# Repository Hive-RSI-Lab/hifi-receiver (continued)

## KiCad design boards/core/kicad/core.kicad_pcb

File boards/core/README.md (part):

# core: the Plus/Ultra main board

The main board of hifi-receiver-2's **Plus** and **Ultra** tiers
([docs/product.md](../../docs/product.md)). It is a USB-C-powered
streaming amplifier on one 4-layer board, 154.4 x 113 mm (120 x 100 until the
banana sockets; see below):

- **Input:** 28 V USB PD EPR at up to 140 W.
- **Streaming:** ESP32 with Wi-Fi, Bluetooth and Ethernet.
- **Mains DAC:** Sabre ES9018K2M.
- **Subwoofers:** a separate sub DAC for two sub outputs.
- **Line in:** RCA, with a zero-latency "DJ direct" path.
- **Amp:** two TPA3220 class-D amps (the pad-down TPA3221): 2 x 77 W into 4 ohm peak, no heatsink. Plus plays L on zone A and R on zone B; Ultra drives two pairs.
- **Ultra population options:** a second amp (zone B), an optical input
  and the FFC to the `ultra-front` display board.

It was designed with the hive-hwde module (KiCad 10, JLCPCB) on 2026-10-28,
from schematic through routed layout to a JLC fab package. **Nothing has
been ordered. Ordering is the person's.**

## Status (2026-10-29)

All hwde gates pass on the routed board after the first-spin review ECO, with hive-hwde at c23e27e:

| Gate | Result |
|---|---|
| `erc` | 0 errors, 0 warnings |
| `place` | pass |
| `drc_routed` | 0 errors, 0 warnings, parity clean |
| `verify` | pass, 1 waiver (`reports/verify-waivers.json`: the ESP32 module's 3V3 decoupling loop) |
| `dfm` | pass on the exported Gerbers |

The fab package is in `fab/`:

- **Gerbers:** `core_gerbers.zip`.
- **Plus build:** `BOM.csv` (88 lines, every one with an LCSC number), `CPL.csv` (298 placed parts, 14 of them on the bottom: see `fab/ORDERING.md`), `BOM-full.csv` and `prebuy.csv`, which lists the Extended parts.
- **Ultra build:** `fab/ultra/` holds `BOM.csv` and `CPL.csv` (302 placed parts) for the same Gerbers.

Board facts:

- **Size:** 4 layers, 154.4 x 113 mm overall, 1.6 mm. The right-hand 34.4 mm
  is a wing along the rear only (y < 150 in KiCad); the front right stays
  notched so the ESP32's antenna is still at the board edge.
- **Stackup:** 4 layers, 1.6 mm, 1 oz outer and 1 oz inner. JLC04161H-1080B
  comes only with 0.5 oz inner, so leave Specify Stackup at no requirement
  on the quote page: JLC then builds a 0.203 mm 7628 prepreg and a 1.03 mm
  core, and a named 1 oz layup adds $51.20. No net here is impedance
  controlled. Order it with
  epoxy filled and capped vias (`fab/ORDERING.md`), and inner copper 1 oz, not JLC's 0.5 oz default: the In2 VBUS/PVDD planes carry
  the full 5 A on their own (`power_trunk.py`).
- **Vias:** 0.7/0.3 mm, plus a few 0.45/0.2 mm GND taps.
- **Mounting:** 4 x M3 plated holes.
- **Holes:** JLC's 0.5 mm hole-to-hole spacing is held everywhere.

hwde's own estimate for 10 boards with assembly is $278, $27.84 each. That
excludes the parts, and it is a lower bound: the PCB line has the
oversize-area bug that hive-hwde issue #12 fixes. JLC's cart is the real quote.

## What's on it

The full block list, the ESP32 GPIO map, the I/O expander map, the FFC
pinout and the power tree are in
[architecture/blocks.md](architecture/blocks.md). In short:

| Block | Parts |
|---|---|
| Power in | GCT USB4085-GF-A through-hole USB-C (48 V/5 A, 240 W), CH224Q PD sink (asks for 28 V; ESP32 can read it or change it over I2C), SMBJ30A TVS, 10 mΩ shunt + INA186 current sense |
| PVDD switch | AO4485 P-FET, on only when firmware sets PVDD_EN **and** the CH224Q's PG says the contract is good; ~60 ms soft start (0.47 A, 9.8 W peak); gross-overvoltage cut-off |
| Rails | SY8303 VBUS to 5.1 V; SY8089 5 V to 3.3 V; LP5907 3.3 V analog; ferrite-fed +5VA and +3V3E |
| Processor | ESP32-WROVER-E-N8R8; CH340B USB-serial on the same USB-C (auto-reset, flashing from a laptop) |
| Ethernet | LAN8720A + HR911105A magjack, gated 50 MHz RMII clock |
| Mains DAC | ES9018K2M at 49.152 MHz MCLK, OPA1678 differential-to-single-ended stage |
| Sub DAC | PCM5102A to a stacked dual RCA (SUB1, SUB2) |
| Line in | stacked dual RCA, ES7243E ADC, TS5A23157 DAC/DJ-direct selector |
| Self-measurement | zone A's A_SPK_L+/R+ through 150k/10k, 470 pF, 1 uF onto a 1.65 V bias; TS5A23157 U20 picks RCA input (default) or the taps for the ADC; select from expander P17 through Q7 |
| Zone A amp | TPA3220 (24 dB, AD mode, 600 kHz; pad down, 15 vias into the GND planes), 10 µH / 10 A filters, 4 board-mounted 4 mm banana sockets |
| Zone B amp [Ultra] | the same, synchronised to zone A as a peripheral |
| Control | TCA9539 I/O expander (0x74, reset with the ESP32's EN); Plus front-edge knob, 2 buttons, IR receiver, status LED |
| Optical [Ultra] | PLR237 TOSLINK into the ES9018K2M's S/PDIF mux |
| Front board [Ultra] | 20-pin 0.5 mm FFC to `ultra-front` |

## Plus and Ultra from one board

| Parts | Plus | Ultra |
|---|---|---|
| zone B amp, its filters, bulk cap (U16, L5-L8, C3xx/R3xx) | fitted (plays R) | fitted |
| speaker sockets J20/J21 (zone A L), J26/J27 (zone B R) | fitted | fitted |
| speaker sockets J22/J23 (zone A R), J24/J25 (zone B L) | not fitted | fitted |
| TOSLINK U19, FB3, C126 | not fitted | fitted |
| FFC J3, R402/R403 | not fitted | fitted |
| knob SW1, buttons SW2/SW3, IR U18 (+R400/C400) | fitted | not fitted |

`fab/BOM.csv`/`CPL.csv` are the **Plus** build. `fab/ultra/BOM.csv` and
`CPL.csv` are the **Ultra** build of the same Gerbers.

## Banana sockets (2026-11-01, issues #117, #124)

The speaker outputs are eight 4 mm banana sockets in one row along the rear
edge, 11 mm apart. From the left in KiCad (from behind the box it reads
right to left): J20 A L+, J21 A L-, J22 A R+, J23 A R-, J24 B L+, J25 B L-,
J26 B R+, J27 B R-. Red is +. Plus plays L on zone A and R on zone B
(`HIFI_SPLIT`), so it fits J20/J21 and J26/J27; Ultra fits all eight.

A socket reaches 21.4 mm into the board and its nose stands 2.65 mm past the
edge, so the board grew. The rear edge moved 13 mm back, and a 34.4 mm wing
on the right took the RCA jacks J4/J5 and the TOSLINK U19. They moved with
D7/D8, FB3 and C126 and the copper between them as one block. The mounting
holes H1/H2 went to the new rear corners (H2 later moved south along the east edge to (185.45, 127.4), to make room for the jacks' side ears: `kicad/gen/rca_ear_eco.py`). How it was done, from
`boards/core`, KiCad's python as `python3.11`:

1. `kicad/gen/blocks_amp.py`: the sockets replace the terminals. Then
   `hwde lib_pull --lcsc C7437321 C7437322`, `build.py` (only amp_a/amp_b
   kept), `parts/*.json` by hand, and the netlist.
2. `python3.11 kicad/gen/banana_eco.py kicad/core.kicad_pcb`: rips the old
   terminal copper and the stitch vias under the row, and cuts the speaker
   pours back to y 130. It moves the rear block and the holes, and redraws
   the outline and the planes.
3. `hwde board_update --placements kicad/gen/banana_placements.json`.
4. `python3.11 kicad/gen/banana_route.py kicad/core.kicad_pcb`: one
   staircase pour per speaker net from its old pour to its socket's pin 2.
   L-/R+ run on F.Cu and L+/R- on B.Cu, four per layer, with no crossings
   and no vias. The pours are 2 mm wide (3.7 A rms). Where a later band
   crosses below a socket, its pin 1 joins pin 2 by a 1 mm In2 link (J23,
   J24, J25).
5. `python3.11 kicad/gen/banana_snub.py kicad/core.kicad_pcb`: zone A R- and
   zone B L+'s snubbers reached their net through the old terminal pin. Each
   gets a via and a B.Cu stub into its pour.
6. `miniroute.py` relays SUB1/SUB2_OUT, LIN_L/LIN_R and OPT_SPDIF to the
   moved block. Each line still goes into its ESD clamp (D7/D8) before the
   jack. Stale stubs are ripped with `rip_at.py`, and
   `kicad/gen/banana_silk.py` drops the sockets' silk, as on Lite.
   `kicad/gen/banana_45.py` puts the route ends back on the 45-degree grid
   (hwde check_route_style).

Folded in from review 5: R5-PA-1 (C4 220 nF/50 V C344195, C8 4.7 uF/25 V
C1779: Q1's soft start stays in its SOA), the EP paste windows off the vias
for U9/U10/U13 (`kicad/gen/ep_paste.py`, hwde check_ep_paste), and the
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
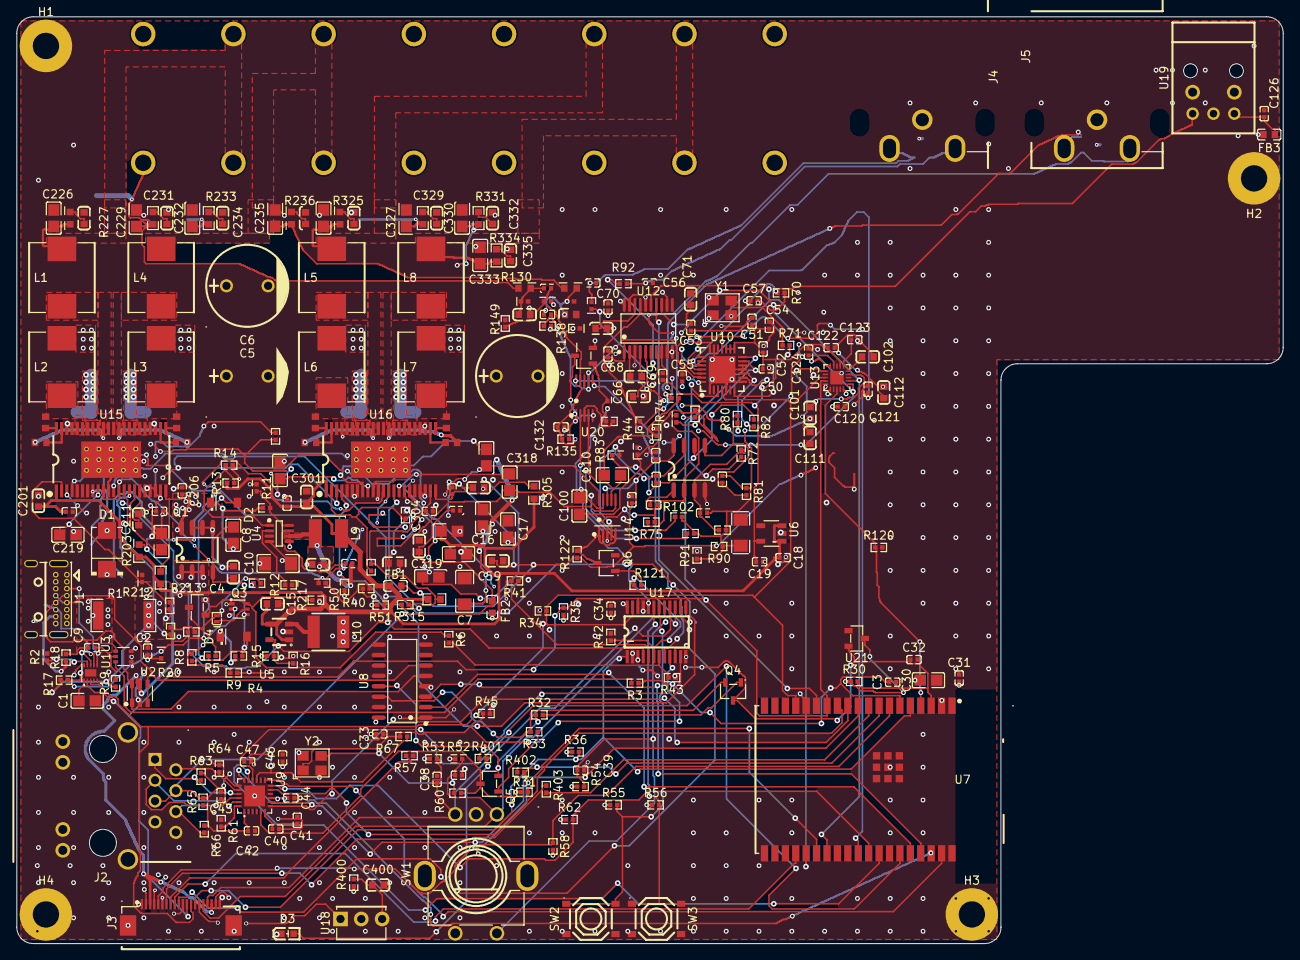
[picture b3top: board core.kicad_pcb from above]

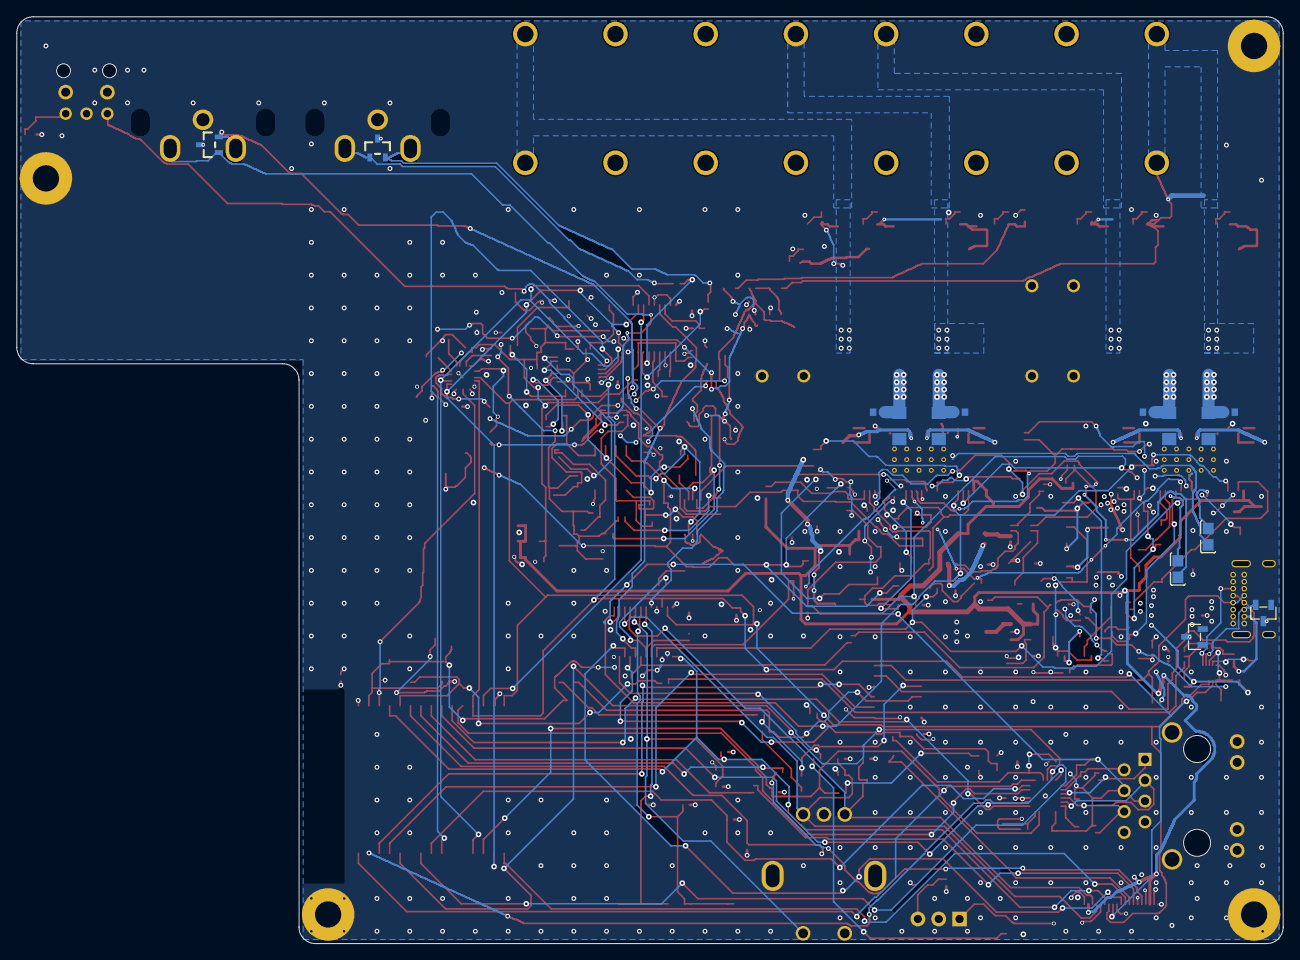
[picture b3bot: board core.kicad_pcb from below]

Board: 4 copper layers, 154.4 x 113.0 mm, 312 parts (14 on the bottom side), 190 nets.

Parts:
C1, C226, C229, C232, C235, C324, C327, C330, C333: 1uF; C0805
C2, C9, C31, C33, C34, C41, C42, C43, C44, C45, C46, C51, C53, C54, C55, C57, C58, C120, C121, C125, C126, C132, C202, C302: 100nF; C0402
C3, C12, C37, C38, C39: 10nF; C0402
C4: 220nF; C0603
C5, C6, C311: 470uF/50V; CAP-TH_BD10.0-P5.00-D1.0-FD
C7, C10: 10uF; C1206
C8, C100, C110: 4.7uF; C0805
C11, C208, C210, C308, C310: 100nF; C0603
C13, C14, C16, C17, C30: 22uF; C0805
C15, C21, C22, C59, C201, C301: 10uF; C0603
C18, C19, C32, C40, C47, C50, C52, C68, C69, C70, C122, C123, C124, C131, C137, C204, C206, C304, C306: 1uF; C0402
C56, C101, C102, C111, C112, C400: 4.7uF; C0603
C64: 100uF; C1206
C65, C66, C67: 2.2uF; C0603
C71, C72, C142, C143, C150, C151: 1nF; C0402
C130, C136: 470pF; C0603
C207, C209, C307, C309: 1uF; C1206
C211, C222, C223, C224, C225, C312, C320, C321, C322, C323: 33nF; C0603
C218, C219, C220, C221, C316, C317, C318, C319: 10uF; C0805
C228, C231, C234, C237, C326, C329, C332, C335: 470nF; C0603
D1: SMBJ30A; SMB_L4.6-W3.6-LS5.3-RD
D2: BZT52C33; SOD-123_L2.7-W1.6-LS3.7-RD
D3: KT-0603R; LED-SMD_L1.6-W0.8-R-RD
D4: BZT52C15; SOD-123_L2.7-W1.6-LS3.7-RD
D5: BAS16L; SOD-882_L1.0-W0.6-RD
D6, D9: NUP2105L; SOT-23-3_L2.9-W1.3-P1.90-LS2.4-BL-2
D7, D8: PESD5V0S2BT; SOT-23_L2.9-W1.3-P1.90-LS2.4-BR
FB1, FB2, FB3: 120R; L0603
H1, H2, H3, H4: MountingHole_3.2mm_M3_Pad
J1: USB4085-GF-A; USC-C-SMD_USB4085-GF-A
J2: HR911105A; RJ45-TH_HR911105A
J3: FFC 20P; FPC-SMD_20P-P0.50_XUNPU_FPC-05F-20PH20
J4: SUB OUT; CONN-TH_XDJK-0271-1650
J5: LINE IN; CONN-TH_XDJK-0271-1650
J20, J22, J24, J26: 24.243 red; CONN-TH_24.243.1_RED
J21, J23, J25, J27: 24.243 black; CONN-TH_24.243.2
L1, L2, L3, L4, L5, L6, L7, L8: 10uH; IND-SMD_L8.5-W8.0_PCC-M0854M
L9: 4.7uH; IND-SMD_L4.0-W4.0
L10: 2.2uH; IND-SMD_L4.0-W4.0_LQH44PN2R2MP0L
Q1: AO4485; SOIC-8_L5.0-W4.0-P1.27-LS6.0-BL
Q2: 2N7002; SOT-23-3_L2.9-W1.3-P1.90-LS2.4-BR
Q3: MMDT3904; SOT-363_L2.0-W1.3-P0.65-LS2.1-TL
Q4, Q5, Q6, Q7: S8050; SOT-23-3_L3.0-W1.7-P0.95-LS2.9-BR
R1: 10m; R2512
R2: 210k; R0402
R3, R6: 1k; R0402
R4, R5: 470k; R0402
R7, R10, R11, R12, R15, R40, R41, R42, R43, R44, R102, R112, R120, R132, R134, R138, R149, R150, R213, R214, R215, R404: 100k; R0402
R8, R9, R20, R30, R31, R32, R33, R36, R50, R51, R52, R53, R54, R55, R56, R57, R58, R67, R70, R121, R122, R131, R135, R137: 10k; R0402
R13: 15k; R0402
R14, R72, R74, R80, R82: 2k; R0402
R16: 22k; R0402
R17, R18, R19: 10R; R0402
R34, R35, R45: 2.2k; R0402
R60, R71, R402, R403: 33R; R0402
R61: 12k; R0402
R62: 1.5k; R0402
R63, R64, R65, R66: 49.9R; R0402
R73, R75, R81, R83: 1.3k; R0402
R90, R91, R92, R93, R401: 470R; R0402
R100, R101, R110, R111: 4.7k; R0402
R130, R136: 150k; R0603
R133, R216, R217, R314: 47k; R0402
R203, R205, R227, R230, R233, R236, R303, R305, R325, R328, R331, R334: 4.7R; R0603
R212: 20k; R0402
R313: 75k; R0402
R315: 0R; R0402
R400: 100R; R0402
SW1: EC11; SW-TH_EC11E1820402
SW2: BTN1; SW-SMD_4P-L5.1-W5.1-P3.70-LS6.5-TL_H1.5
SW3: BTN2; SW-SMD_4P-L5.1-W5.1-P3.70-LS6.5-TL_H1.5
U1: CH224Q; DFN-10_L2.0-W2.0-P0.40-BL-EP
U2: USBLC6-2SC6; SOT-23-6_L2.9-W1.6-P0.95-LS2.8-BL
U3: INA186A1; SC-70-6_L2.2-W1.3-P0.65-LS2.1-BR
U4: SY8303AIC; TSOT-23-8_L2.9-W1.6-P0.65-LS2.8-BR
U5: SY8089A1AAC; TSOT-23-5_L2.9-W1.6-P0.95-LS2.8-BR
U6: LP5907-3.3; SOT-23-5_L3.0-W1.7-P0.95-LS2.8-BR
U7: ESP32-WROVER-E-N8R8; WIFI-SMD_ESP32-WROVER-IE8MB
U8: CH340B; SOP-16_L10.0-W3.9-P1.27-LS6.0-BL
U9: LAN8720A; QFN-24_L4.0-W4.0-P0.50-BL-EP2.6
U10: ES9018K2M; QFN-28_L5.0-W5.0-P0.50-BL-EP3.3
U11: OPA1678; SOIC-8_L5.0-W4.0-P1.27-LS6.0-BL
U12: PCM5102A; TSSOP-20_L6.5-W4.4-P0.65-LS6.4-BL
U13: ES7243E; QFN-20_L3.0-W3.0-P0.40-BL-EP1.7
U14, U20: TS5A23157; MSOP-10_L3.0-W3.0-P0.50-LS5.0-BL
U15, U16: TPA3220; HTSSOP-44-1EP_L14.0-W6.1-P0.64-LS8.1-EP7.3x4.43
U17: TCA9539; TSSOP-24_L7.8-W4.4-P0.65-LS6.4-BL
U18: IRM-3638T; OPTO-TH_IRM-3638T
U19: PLR237/T8BK; OPTO-TH_PLR237-T10BK
U21: TLV803S; SOT-23-3_L2.9-W1.3-P1.90-LS2.4-BR
Y1: 49.152MHz; OSC-SMD_4P-L3.2-W2.5-BL
Y2: 50MHz; OSC-SMD_4P-L3.2-W2.5-BL

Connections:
+3V3: C2.1, C16.1, C17.1, C30.1, C31.1, C33.1, C34.1, C44.1, C46.1, C55.1, C57.1, C70.1, C120.1, C121.1, FB2.1, FB3.1, J3.2, J3.19, L10.2, R15.1, R20.1, R30.1, R31.1, R34.1, R35.1, R36.1, R50.1, R51.1, R52.1, R53.1, R54.1, R55.1, R56.1, R58.1, R62.1, R132.2, R138.2, R400.1, U3.3, U7.2, U8.4, U8.16, U9.9, U10.18, U12.20, U13.1, U13.5, U17.24, U21.3, Y1.1, Y1.4, Y2.4
+3V3A: C19.1, C50.1, C51.1, C52.1, C53.1, C54.1, C68.1, C69.1, C122.1, U6.5, U10.15, U10.16, U10.17, U12.1, U12.8, U13.12
+3V3E: C22.1, C42.1, C43.1, C45.1, FB2.2, J2.4, J2.5, R63.2, R64.2, R65.2, R66.2, U9.1, U9.19
+5V: C13.1, C14.1, C15.1, C18.1, C201.1, C202.1, C301.1, C302.1, FB1.1, J3.3, J3.18, L9.2, R13.1, R203.1, R205.1, R303.1, R305.1, U2.5, U5.1, U5.4, U6.1, U6.3, U15.1, U16.1
+5VA: C21.1, C58.1, C59.1, C125.1, C132.1, FB1.2, R90.1, R122.1, R135.1, U11.8, U14.8, U20.8
/AMP_A_RST: R40.1, U15.10, U17.4
/AMP_B_RST: R41.1, U16.10, U17.5
/AMP_FAULT: R50.2, U15.4, U16.4, U17.13
/AMP_IN_L: C218.1, C316.1, U14.10
/AMP_IN_R: C220.1, C318.1, U14.6
/AMP_OSCM: R216.1, U15.12, U16.12
/AMP_OSCP: R217.1, U15.13, U16.13
/AMP_OTW: R51.2, U15.3, U16.3, U17.14
/A_SPK_L+: C229.1, J20.1, J20.2, L2.2, R130.1, R230.1
/A_SPK_R+: C235.1, J22.1, J22.2, L4.2, R136.1, R236.1
/BTN_1: R55.2, SW2.1, SW2.2, U17.18
/BTN_2: R56.2, SW3.1, SW3.2, U17.19
/DAC_EN: R44.1, U10.28, U12.17, U17.8
/DJ_DIRECT: R42.1, R121.1, U17.6
/ENC_A: C37.1, J3.16, R52.2, SW1.A, U17.15
/ENC_B: C38.1, J3.17, R53.2, SW1.B, U17.16
/ENC_SW: C39.1, R54.2, SW1.D, U17.17
/ETH_CLK: Q5.3, R31.2, R60.2, U7.25, U9.5
/EXP_INT: J3.14, R36.2, U7.5, U17.1
/I2C_SCL: J3.12, R35.2, U1.2, U7.13, U10.3, U13.19, U17.22
/I2C_SDA: J3.13, R34.2, U1.3, U7.16, U10.4, U13.18, U17.23
/I2S_BCK: U7.24, U10.27, U12.13, U13.6
/I2S_DIN: R120.1, U7.4, U13.3
/I2S_DOUT_MAIN: U7.29, U10.25
/I2S_DOUT_SUB: U7.14, U12.14
/I2S_LRCK: U7.26, U10.26, U12.15, U13.7
/IR_IN: J3.15, R58.2, U7.7, U18.1
/ISENSE: C3.1, R3.2, U7.6
/LCD_BL: J3.10, U17.10
/LCD_CS: J3.8, R57.1
/LCD_DC: J3.9, U7.23
/LCD_MOSI: R403.1, U7.9
/LCD_SCLK: R402.1, U7.8
/LED_STATUS: R401.1, U17.11
/MAIN_L: C143.2, R75.2, U11.1, U14.2
/MAIN_R: C151.2, R83.2, U11.7, U14.4
/MDC: U7.37, U9.13
/MDIO: R62.2, U7.30, U9.12
/OPT_SPDIF: R70.1, U10.24, U19.3
/PHY_RST: R45.1, R67.1, U17.9, Y2.1
/PVDD_EN: R6.1, R43.1, U17.7
/RMII_CRS_DV: U7.12, U9.11
/RMII_RXD0: U7.10, U9.8
/RMII_RXD1: U7.11, U9.7
/RMII_TXD0: U7.31, U9.17
/RMII_TXD1: U7.36, U9.18
/RMII_TX_EN: U7.33, U9.16
/TAP_SEL_IO: R133.1, U17.20
/USB_DM: J1.A7, J1.B7, U2.3, U2.4, U8.6
/USB_DP: J1.A6, J1.B6, U2.1, U2.6, U8.5
/VREF: C64.1, C142.2, C150.2, R73.2, R81.2, R90.2, R91.1, R102.2, R112.2
/amp_a/A_AVDD: C204.1, R203.2, R213.2, R216.2, U15.21
/amp_a/A_BST1M: C222.1, U15.43
/amp_a/A_BST1P: C223.1, U15.44
/amp_a/A_BST2M: C224.1, U15.23
/amp_a/A_BST2P: C225.1, U15.24
/amp_a/A_CMUTE: C211.1, U15.17
/amp_a/A_FREQ: R214.1, R215.1, U15.14
/amp_a/A_GAIN: R212.1, R213.1, U15.2
/amp_a/A_GVDD: C206.1, R205.2, U15.22
/amp_a/A_IN1M: C219.1, U15.9
/amp_a/A_IN1P: C218.2, U15.8
/amp_a/A_IN2M: C221.1, U15.16
/amp_a/A_IN2P: C220.2, U15.15
/amp_a/A_OUT1M: C222.2, L1.1, U15.35
/amp_a/A_OUT1M_SN: C228.1, R227.2
/amp_a/A_OUT1P: C223.2, L2.1, U15.39, U15.40
/amp_a/A_OUT1P_SN: C231.1, R230.2
/amp_a/A_OUT2M: C224.2, L3.1, U15.27, U15.28
/amp_a/A_OUT2M_SN: C234.1, R233.2
/amp_a/A_OUT2P: C225.2, L4.1, U15.32
/amp_a/A_OUT2P_SN: C237.1, R236.2
/amp_a/A_SPK_L-: C226.1, J21.1, J21.2, L1.2, R227.1
/amp_a/A_SPK_R-: C232.1, J23.1, J23.2, L3.2, R233.1
/amp_b/B_AVDD: C304.1, R303.2, R314.2, R315.2, U16.21
/amp_b/B_BST1M: C320.1, U16.43
/amp_b/B_BST1P: C321.1, U16.44
/amp_b/B_BST2M: C322.1, U16.23
/amp_b/B_BST2P: C323.1, U16.24
/amp_b/B_CMUTE: C312.1, U16.17
/amp_b/B_FREQ: R315.1, U16.14
/amp_b/B_GAIN: R313.1, R314.1, U16.2
/amp_b/B_GVDD: C306.1, R305.2, U16.22
/amp_b/B_IN1M: C317.1, U16.9
/amp_b/B_IN1P: C316.2, U16.8
/amp_b/B_IN2M: C319.1, U16.16
/amp_b/B_IN2P: C318.2, U16.15
/amp_b/B_OUT1M: C320.2, L5.1, U16.35
/amp_b/B_OUT1M_SN: C326.1, R325.2
/amp_b/B_OUT1P: C321.2, L6.1, U16.39, U16.40
/amp_b/B_OUT1P_SN: C329.1, R328.2
/amp_b/B_OUT2M: C322.2, L7.1, U16.27, U16.28
/amp_b/B_OUT2M_SN: C332.1, R331.2
/amp_b/B_OUT2P: C323.2, L8.1, U16.32
/amp_b/B_OUT2P_SN: C335.1, R334.2
/amp_b/B_SPK_L+: C327.1, J24.1, J24.2, L6.2, R328.1
/amp_b/B_SPK_L-: C324.1, J25.1, J25.2, L5.2, R325.1
/amp_b/B_SPK_R+: C333.1, J26.1, J26.2, L8.2, R334.1
/amp_b/B_SPK_R-: C330.1, J27.1, J27.2, L7.2, R331.1
/dac/DACL_N: R72.1, U10.14
/dac/DACL_P: R74.1, U10.13
/dac/DACR_N: R80.1, U10.10
/dac/DACR_P: R82.1, U10.9
/dac/DAC_DVDD: C56.1, U10.21
/dac/DAC_MCLK: R71.2, U10.7
/dac/OPL_N: C143.1, R74.2, R75.1, U11.2
/dac/OPL_P: C142.1, R72.2, R73.1, U11.3
/dac/OPR_N: C151.1, R82.2, R83.1, U11.6
/dac/OPR_P: C150.1, R80.2, R81.1, U11.5
/dac/OSC_OUT: R71.1, Y1.3
/dac/SUB1_DAC: R92.1, U12.6
/dac/SUB1_OUT: C71.1, D7.1, J4.1, R92.2
/dac/SUB2_DAC: R93.1, U12.7
/dac/SUB2_OUT: C72.1, D7.2, J4.3, R93.2
/dac/SUB_CAPM: C65.2, U12.4
/dac/SUB_CAPP: C65.1, U12.2
/dac/SUB_LDOO: C67.1, U12.18
/dac/SUB_VNEG: C66.1, U12.5
/ethernet/ETH_OSC: R60.1, Y2.3
/ethernet/ETH_RXN: J2.6, R66.1, U9.22
/ethernet/ETH_RXP: J2.3, R65.1, U9.23
/ethernet/ETH_TXN: J2.2, R64.1, U9.20
/ethernet/ETH_TXP: J2.1, R63.1, U9.21
/ethernet/PHY_NRST: C47.1, R67.2, U9.15
/ethernet/PHY_RBIAS: R61.1, U9.24
/ethernet/PHY_VDDCR: C40.1, C41.1, U9.6
/linein/ADC_LN: C102.1, U13.10
/linein/ADC_LP: C101.2, U13.9
/linein/ADC_REFP: C124.1, U13.14
/linein/ADC_REFQ: C123.1, U13.11
/linein/ADC_RN: C112.1, U13.15
/linein/ADC_RP: C111.2, U13.16
/linein/ADC_SRC_L: C101.1, U20.10
/linein/ADC_SRC_R: C111.1, U20.6
/linein/DJ_B: Q6.1, R121.2
/linein/DJ_SEL: Q6.3, R122.2, U14.1, U14.5
/linein/LDIV_L: C100.1, R100.2, R101.1
/linein/LDIV_R: C110.1, R110.2, R111.1
/linein/LIN_L: D8.1, J5.1, R100.1
/linein/LIN_R: D8.2, J5.3, R110.1
/linein/LSW_L: C100.2, R102.1, U14.9, U20.2
/linein/LSW_R: C110.2, R112.1, U14.7, U20.4
/linein/OPT_VCC: C126.1, FB3.2, U19.1
/linein/TAPA_L: C130.1, C131.1, R130.2, R131.1
/linein/TAPA_R: C136.1, C137.1, R136.2, R137.1
/linein/TAP_B: Q7.1, R133.2, R134.1
/linein/TAP_L: C131.2, R132.1, R149.1, U20.9
/linein/TAP_R: C137.2, R138.1, R150.1, U20.7
/linein/TAP_SEL: Q7.3, R135.2, U20.1, U20.5
/mcu/AR_B1: Q4.1, R32.2
/mcu/AR_B2: Q5.1, R33.2
/mcu/ESP_EN: C32.1, Q4.3, R30.2, U7.3, U17.3, U21.2
/mcu/U0RXD: U7.34, U8.2
/mcu/U0TXD: U7.35, U8.3
/mcu/UART_DTR: Q5.2, R32.1, U8.13
/mcu/UART_RTS: Q4.2, R33.1, U8.14
/power_in/CC1: D6.1, J1.A5, U1.6
/power_in/CC2: D9.2, J1.B5, U1.7
/power_in/ISENSE_RAW: R3.1, U3.6
/power_in/ISNS_N: C9.2, R19.2, U3.5
/power_in/ISNS_P: C9.1, R18.2, U3.4
/power_in/OV_B: Q3.2, R8.2, R9.1
/power_in/OV_Z: D2.2, R8.1
/power_in/PD_CFG1: R2.1, U1.9
/power_in/PD_PG: Q2.2, R20.2, U1.10
/power_in/PVDD_ENG: Q2.1, Q3.6, R6.2, R7.1
/power_in/PVDD_G: C4.1, C8.2, D4.2, Q1.4, Q3.4, R4.2, R5.1
/power_in/PVDD_OFFB: D5.1, Q3.5
/power_in/PVDD_PD: D5.2, Q2.3, R5.2, R404.2
/power_in/VBUS_PD: C1.1, R17.2, U1.1, U1.8
/rails/BUCK3_FB: R15.2, R16.1, U5.5
/rails/BUCK3_LX: L10.1, U5.3
/rails/BUCK5_BS: C12.1, U4.7
/rails/BUCK5_EN: R10.2, R11.1, U4.8
/rails/BUCK5_FB: R13.2, R14.1, U4.1
/rails/BUCK5_FS: R12.1, U4.2
/rails/BUCK5_LX: C12.2, L9.1, U4.6
/ui/FFC_MOSI: J3.7, R403.2
/ui/FFC_SCK: J3.5, R402.2
/ui/IR_VCC: C400.1, R400.2, U18.3
/ui/LED_A: D3.1, R401.2
GND: C1.2, C2.2, C3.2, C5.2, C6.2, C7.2, C10.2, C11.2, C13.2, C14.2, C15.2, C16.2, C17.2, C18.2, C19.2, C21.2, C22.2, C30.2, C31.2, C32.2, C33.2, C34.2, C37.2, C38.2, C39.2, C40.2, C41.2, C42.2, C43.2, C44.2, C45.2, C46.2, C47.2, C50.2, C51.2, C52.2, C53.2, C54.2, C55.2, C56.2, C57.2, C58.2, C59.2, C64.2, C66.2, C67.2, C68.2, C69.2, C70.2, C71.2, C72.2, C102.2, C112.2, C120.2, C121.2, C122.2, C123.2, C124.2, C125.2, C126.2, C130.2, C132.2, C136.2, C201.2, C202.2, C204.2, C206.2, C207.2, C208.2, C209.2, C210.2, C211.2, C219.2, C221.2, C226.2, C228.2, C229.2, C231.2, C232.2, C234.2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
PVDD: C4.2, C5.1, C6.1, C7.1, C207.1, C208.1, C209.1, C210.1, C307.1, C308.1, C309.1, C310.1, C311.1, Q1.5, Q1.6, Q1.7, Q1.8, U15.29, U15.30, U15.31, U15.36, U15.37, U15.38, U16.29, U16.30, U16.31, U16.36, U16.37, U16.38
VBUS: C8.1, C10.1, C11.1, D2.1, D4.1, Q1.1, Q1.2, Q1.3, Q3.3, R1.2, R4.1, R10.1, R17.1, R19.1, R404.1, U4.5
VBUS_IN: D1.1, J1.A4, J1.A9, J1.B4, J1.B9, R1.1, R18.1

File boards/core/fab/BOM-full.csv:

Comment,Designator,Qty Per Board,Footprint,MPN,LCSC,Assembly Class,Instructions
1uF,"C1,C226,C229,C232,C235,C324,C327,C330,C333",9,C0805,1uF,C28323,smt_placed,
100nF,"C2,C31,C33,C34,C41,C42,C43,C44,C45,C46,C51,C53,C54,C55,C57,C58,C120,C121,C125,C132,C202,C302",22,C0402,100nF,C1525,smt_placed,
10nF,"C3,C12,C37,C38,C39",5,C0402,10nF,C15195,smt_placed,
220nF,C4,1,C0603,TCC0603X7R224K500CT,C344195,smt_placed,
470uF/50V,"C5,C6,C311",3,CAP-TH_BD10.0-P5.00-D1.0-FD,470uF/50V,C88733,smt_placed,
10uF,"C7,C10",2,C1206,10uF,C13585,smt_placed,
4.7uF,"C8,C100,C110",3,C0805,4.7uF,C1779,smt_placed,
100nF,C9,1,C0402,100nF,C307331,smt_placed,
100nF,"C11,C208,C210,C308,C310",5,C0603,100nF,C14663,smt_placed,
22uF,"C13,C14,C16,C17,C30",5,C0805,22uF,C45783,smt_placed,
10uF,"C15,C21,C22,C59,C201,C301",6,C0603,10uF,C19702,smt_placed,
1uF,"C18,C19,C32,C40,C47,C50,C52,C68,C69,C70,C122,C123,C124,C131,C137,C204,C206,C304,C306",19,C0402,1uF,C52923,smt_placed,
4.7uF,"C56,C101,C102,C111,C112,C400",6,C0603,4.7uF,C19666,smt_placed,
100uF,C64,1,C1206,100uF,C15008,smt_placed,
2.2uF,"C65,C66,C67",3,C0603,2.2uF,C23630,smt_placed,
1nF,"C71,C72,C142,C143,C150,C151",6,C0402,1nF,C1523,smt_placed,
470pF,"C130,C136",2,C0603,470pF,C1620,smt_placed,
1uF,"C207,C209,C307,C309",4,C1206,TCC1206X7R105K101HT,C282823,smt_placed,
33nF,"C211,C222,C223,C224,C225,C312,C320,C321,C322,C323",10,C0603,33nF,C21117,smt_placed,
10uF,"C218,C219,C220,C221,C316,C317,C318,C319",8,C0805,10uF,C15850,smt_placed,
470nF,"C228,C231,C234,C237,C326,C329,C332,C335",8,C0603,CC0603KRX7R9BB474,C513577,smt_placed,
SMBJ30A,D1,1,SMB_L4.6-W3.6-LS5.3-RD,SMBJ30A,C113998,smt_placed,
BZT52C33,D2,1,SOD-123_L2.7-W1.6-LS3.7-RD,BZT52C33,C266574,smt_placed,
KT-0603R,D3,1,LED-SMD_L1.6-W0.8-R-RD,KT-0603R,C2286,smt_placed,
BZT52C15,D4,1,SOD-123_L2.7-W1.6-LS3.7-RD,BZT52C15,C173427,smt_placed,
BAS16L,D5,1,SOD-882_L1.0-W0.6-RD,BAS16L,C99382,smt_placed,
NUP2105L,"D6,D9",2,SOT-23-3_L2.9-W1.3-P1.90-LS2.4-BL-2,NUP2105LT1G,C14486,smt_placed,
PESD5V0S2BT,"D7,D8",2,SOT-23_L2.9-W1.3-P1.90-LS2.4-BR,"PESD5V0S2BT,215",C49338,smt_placed,
120R,"FB1,FB2",2,L0603,120R,C14709,smt_placed,
USB4085-GF-A,J1,1,USC-C-SMD_USB4085-GF-A,USB4085-GF-A,C7095263,smt_placed,
HR911105A,J2,1,RJ45-TH_HR911105A,HR911105A,C12074,smt_placed,
SUB OUT,J4,1,CONN-TH_XDJK-0271-1650,XDJK-0271-1650,C7527522,smt_placed,
LINE IN,J5,1,CONN-TH_XDJK-0271-1650,XDJK-0271-1650,C7527522,smt_placed,
24.243 red,"J20,J26",2,CONN-TH_24.243.1_RED,24.243.1,C7437321,smt_placed,
24.243 black,"J21,J27",2,CONN-TH_24.243.2,24.243.2,C7437322,smt_placed,
10uH,"L1,L2,L3,L4,L5,L6,L7,L8",8,IND-SMD_L8.5-W8.0_PCC-M0854M,10uH,C2962885,smt_placed,
4.7uH,L9,1,IND-SMD_L4.0-W4.0,4.7uH,C57269,smt_placed,
2.2uH,L10,1,IND-SMD_L4.0-W4.0_LQH44PN2R2MP0L,2.2uH,C36409,smt_placed,
AO4485,Q1,1,SOIC-8_L5.0-W4.0-P1.27-LS6.0-BL,AO4485,C51499,smt_placed,
2N7002,Q2,1,SOT-23-3_L2.9-W1.3-P1.90-LS2.4-BR,2N7002,C8545,smt_placed,
MMDT3904,Q3,1,SOT-363_L2.0-W1.3-P0.65-LS2.1-TL,MMDT3904,C83572,smt_placed,
S8050,"Q4,Q5,Q6,Q7",4,SOT-23-3_L3.0-W1.7-P0.95-LS2.9-BR,S8050,C2146,smt_placed,
10m,R1,1,R2512,10m,C393070,smt_placed,
210k,R2,1,R0402,210k,C2998176,smt_placed,
1k,"R3,R6",2,R0402,1k,C11702,smt_placed,
470k,"R4,R5",2,R0402,470k,C25790,smt_placed,
100k,"R7,R10,R11,R12,R15,R40,R41,R42,R43,R44,R102,R112,R120,R132,R134,R138,R149,R150,R213,R214,R215,R404",22,R0402,100k,C25741,smt_placed,
10k,"R8,R9,R20,R30,R31,R32,R33,R36,R50,R51,R52,R53,R54,R55,R56,R57,R58,R67,R70,R121,R122,R131,R135,R137",24,R0402,10k,C25744,smt_placed,
15k,R13,1,R0402,15k,C25756,smt_placed,
2k,"R14,R72,R74,R80,R82",5,R0402,2k,C4109,smt_placed,
22k,R16,1,R0402,22k,C25768,smt_placed,
10R,"R17,R18,R19",3,R0402,10R,C25077,smt_placed,
2.2k,"R34,R35,R45",3,R0402,2.2k,C25879,smt_placed,
33R,"R60,R71",2,R0402,33R,C25105,smt_placed,
12k,R61,1,R0402,12k,C25752,smt_placed,
1.5k,R62,1,R0402,1.5k,C25867,smt_placed,
49.9R,"R63,R64,R65,R66",4,R0402,49.9R,C25120,smt_placed,
1.3k,"R73,R75,R81,R83",4,R0402,1.3k,C25866,smt_placed,
470R,"R90,R91,R92,R93,R401",5,R0402,470R,C25117,smt_placed,
4.7k,"R100,R101,R110,R111",4,R0402,4.7k,C25900,smt_placed,
150k,"R130,R136",2,R0603,150k,C22807,smt_placed,
47k,"R133,R216,R217,R314",4,R0402,47k,C25792,smt_placed,
4.7R,"R203,R205,R227,R230,R233,R236,R303,R305,R325,R328,R331,R334",12,R0603,4.7R,C23164,smt_placed,
20k,R212,1,R0402,20k,C25765,smt_placed,
75k,R313,1,R0402,75k,C25798,smt_placed,
0R,R315,1,R0402,0R,C17168,smt_placed,
100R,R400,1,R0402,100R,C25076,smt_placed,
EC11,SW1,1,SW-TH_EC11E1820402,EC11,C361165,smt_placed,
BTN1,SW2,1,SW-SMD_4P-L5.1-W5.1-P3.70-LS6.5-TL_H1.5,TS-1187A-B-A-B,C318884,smt_placed,
BTN2,SW3,1,SW-SMD_4P-L5.1-W5.1-P3.70-LS6.5-TL_H1.5,TS-1187A-B-A-B,C318884,smt_placed,
CH224Q,U1,1,DFN-10_L2.0-W2.0-P0.40-BL-EP,CH224Q,C46061833,smt_placed,
USBLC6-2SC6,U2,1,SOT-23-6_L2.9-W1.6-P0.95-LS2.8-BL,USBLC6-2SC6,C2687116,smt_placed,
INA186A1,U3,1,SC-70-6_L2.2-W1.3-P0.65-LS2.1-BR,INA186A1,C2058311,smt_placed,
SY8303AIC,U4,1,TSOT-23-8_L2.9-W1.6-P0.65-LS2.8-BR,SY8303AIC,C97054,smt_placed,
SY8089A1AAC,U5,1,TSOT-23-5_L2.9-W1.6-P0.95-LS2.8-BR,SY8089A1AAC,C479074,smt_placed,
LP5907-3.3,U6,1,SOT-23-5_L3.0-W1.7-P0.95-LS2.8-BR,LP5907-3.3,C80670,smt_placed,
ESP32-WROVER-E-N8R8,U7,1,WIFI-SMD_ESP32-WROVER-IE8MB,ESP32-WROVER-E-N8R8,C2973667,smt_placed,
CH340B,U8,1,SOP-16_L10.0-W3.9-P1.27-LS6.0-BL,CH340B,C81010,smt_placed,
LAN8720A,U9,1,QFN-24_L4.0-W4.0-P0.50-BL-EP2.6,LAN8720A,C45223,smt_placed,
ES9018K2M,U10,1,QFN-28_L5.0-W5.0-P0.50-BL-EP3.3,ES9018K2M,C2688377,smt_placed,
OPA1678,U11,1,SOIC-8_L5.0-W4.0-P1.27-LS6.0-BL,OPA1678,C192421,smt_placed,
PCM5102A,U12,1,TSSOP-20_L6.5-W4.4-P0.65-LS6.4-BL,PCM5102A,C107671,smt_placed,
ES7243E,U13,1,QFN-20_L3.0-W3.0-P0.40-BL-EP1.7,ES7243E,C2929446,smt_placed,
TS5A23157,"U14,U20",2,MSOP-10_L3.0-W3.0-P0.50-LS5.0-BL,TS5A23157,C11133,smt_placed,
TPA3220,"U15,U16",2,HTSSOP-44-1EP_L14.0-W6.1-P0.64-LS8.1-EP7.3x4.43,TPA3220,C2879306,smt_placed,
TCA9539,U17,1,TSSOP-24_L7.8-W4.4-P0.65-LS6.4-BL,TCA9539,C131972,smt_placed,
IRM-3638T,U18,1,OPTO-TH_IRM-3638T,IRM-3638T,C42421366,smt_placed,
TLV803S,U21,1,SOT-23-3_L2.9-W1.3-P1.90-LS2.4-BR,TLV803SDBZR,C132016,smt_placed,
49.152MHz,Y1,1,OSC-SMD_4P-L3.2-W2.5-BL,49.152MHz,C7431354,smt_placed,
50MHz,Y2,1,OSC-SMD_4P-L3.2-W2.5-BL,50MHz,C717684,smt_placed,
100nF,C126,1,C0402,100nF,C1525,dnp,DO NOT POPULATE - this land ships empty.
120R,FB3,1,L0603,120R,C14709,dnp,DO NOT POPULATE - this land ships empty.
FFC 20P,J3,1,FPC-SMD_20P-P0.50_XUNPU_FPC-05F-20PH20,FFC 20P,C2856803,dnp,DO NOT POPULATE - this land ships empty.
24.243 red,"J22,J24",2,CONN-TH_24.243.1_RED,24.243.1,C7437321,dnp,DO NOT POPULATE - this land ships empty.
24.243 black,"J23,J25",2,CONN-TH_24.243.2,24.243.2,C7437322,dnp,DO NOT POPULATE - this land ships empty.
33R,"R402,R403",2,R0402,33R,C25105,dnp,DO NOT POPULATE - this land ships empty.
PLR237/T8BK,U19,1,OPTO-TH_PLR237-T10BK,PLR237/T8BK,C17223620,dnp,DO NOT POPULATE - this land ships empty.
,"H1,H2,H3,H4",4,,,,board_feature,Realised in copper - nothing to buy or place.

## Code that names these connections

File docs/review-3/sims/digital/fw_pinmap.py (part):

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sg = dict(kv.split('=', 1) for kv in setg.split(','))
ctrls = re.search(r'default "(\[\{\\"gpio\\":13.*?\])" if HIFI_LITE', patch).group(1).replace('\\"', '"')
btn = {int(m.group(1)): m.group(2) for m in re.finditer(r'"gpio":(\d+).*?"pressed":"(ACTRLS_\w+)"', ctrls)}
lite_out = [(int(L['PIN_PVDD_EN']), 'PVDD_EN', 'out'), (int(L['PIN_AMP_SDZ']), 'AMP_SDZ_IO', 'out'),
            (int(L['I2C_SCL']), 'I2C_SCL', 'out'), (int(L['I2C_SDA']), 'I2C_SDA', 'out'),
            (int(d['bck']), 'I2S_BCLK', 'out'), (int(d['ws']), 'I2S_LRCK', 'out'),
            (int(d['do']), 'I2S_DOUT', 'out'), (int(d['mck']), 'I2S_MCLK', 'out'),
            ([int(k) for k, v in sg.items() if 'green' in v][0], 'LED_DRV', 'out')]
lite_in = [(int(L['PIN_PD_PG']), 'PD_PG', 'in'), (int(L['PIN_AMP_FAULTZ']), 'AMP_FAULTZ', 'in'),
           (int(d['di']), 'I2S_DIN', 'in'), ([int(k) for k, v in sg.items() if 'ir' in v][0], 'IR_IN', 'in'),
           (ADC1_CH[int(L['ADC_VBUS'].split('_')[-1])], 'VBUS_SENSE', 'in'),
           (ADC1_CH[int(L['ADC_PVDD'].split('_')[-1])], 'PVDD_SENSE', 'in')]
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i2cc = dict(kv.split('=') for kv in kdefault('I2C_CONFIG', 'HIFI_PLUS').split(','))
core_out = [(int(C['I2C_SCL']), 'I2C_SCL', 'out'), (int(C['I2C_SDA']), 'I2C_SDA', 'out'),
            (int(i2cc['scl']), 'I2C_SCL', 'out'), (int(i2cc['sda']), 'I2C_SDA', 'out'),
            (int(C['PIN_I2S_BCK']), 'I2S_BCK', 'out'), (int(dacc['bck']), 'I2S_BCK', 'out'),
            (int(C['PIN_I2S_LRCK']), 'I2S_LRCK', 'out'), (int(dacc['ws']), 'I2S_LRCK', 'out'),
            (int(dacc['do']), 'I2S_DOUT_MAIN', 'out'), (int(C['PIN_I2S_DOUT_SUB']), 'I2S_DOUT_SUB', 'out'),
            (int(eth['mdc']), 'MDC', 'out'), (int(C['PIN_MDC']), 'MDC', 'out'), (int(eth['mdio']), 'MDIO', 'out'),
            (int(C['PIN_RMII_TXD0']), 'RMII_TXD0', 'out'), (int(C['PIN_RMII_TXD1']), 'RMII_TXD1', 'out'),
            (int(C['PIN_RMII_TX_EN']), 'RMII_TX_EN', 'out')]
core_in = [(int(dacc['di']), 'I2S_DIN', 'in'), (int(C['PIN_EXP_INT']), 'EXP_INT', 'in'),
           (ADC1_CH[int(C['ADC_ISENSE'].split('_')[-1])], 'ISENSE', 'in'),
           ([int(k) for k, v in setc.items() if 'ir' in v][0], 'IR_IN', 'in'),
           (int(C['PIN_ETH_CLK']), 'ETH_CLK', 'in'), (int(C['PIN_RMII_RXD0']), 'RMII_RXD0', 'in'),
           (int(C['PIN_RMII_RXD1']), 'RMII_RXD1', 'in'), (int(C['PIN_RMII_CRS_DV']), 'RMII_CRS_DV', 'in')]
sq_lan = os.environ.get('SQZ_LAN8720_C')   # optional: path to squeezelite's network_driver_LAN8720.c

def core_extra(comps, nets, pn, at):
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            is_in = bool(cfg >> (b % 8) & 1)
            chk(not got.endswith('_IO') or not is_in,
                f"core expander bit {b} (P1{b-8}) is net {got} on the board; firmware has no define for it and leaves it {'an input' if is_in else 'an output'}")
    chk(at(0) == 'ETH_CLK', 'core GPIO0 is the RMII clock input (CONFIG_ETH_RMII_CLK_IN_GPIO=0)')
    strap = netlib.short(pn[('U9', '10')])
    phyad = 1 if strap == '+3V3' else 0   # RXER/PHYAD0 has an internal pull-down (DS00002165C table 3-x, PD)
    want = None
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
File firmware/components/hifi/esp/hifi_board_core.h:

/*
 * The core board's pins and parts (Plus and Ultra), from
 * boards/core/architecture/blocks.md: its ESP32 GPIO map, the I/O expander
 * map and the FFC to Ultra's front board.
 *
 * Squeezelite-esp32 owns I2S0 (the Sabre DAC's data, the line-in ADC's),
 * IR and Ethernet through the Kconfig defaults in firmware/patches. This
 * component owns the I2C bus's other parts: the PD sink, the expander (amp
 * resets and faults, PVDD, the DAC's reset, the PHY's clock, DJ direct, the
 * LED, the knob and buttons) and the current sense, and drives the sub DAC
 * from I2S1.
 */
#pragma once

#include "sdkconfig.h"

#ifdef CONFIG_HIFI_ULTRA
#define HIFI_MODEL "hifi-ultra"
#define HIFI_ZONES 2
#define HIFI_SPLIT 0
#else
#define HIFI_MODEL "hifi-plus"
#define HIFI_ZONES 1
/* Plus fits zone B too and splits the pair: L plays on zone A (J6), R on
 * zone B (J11), one channel per TPA3220, so each chip carries half the heat
 * (docs/review-2/heatsink-options.md). Both amps run whenever the amp is on */
#define HIFI_SPLIT 1
#endif
/* bring-up: the API's LED test (the red LED, and Ultra's front LED) and
 * Ultra's backlight modes (hifi_bsp_set_led, hifi_bsp_set_backlight) */
#define HIFI_HAS_LED_TEST /* no value: the pinmap check reads "NAME <number>" as a GPIO */
#ifdef CONFIG_HIFI_ULTRA
#define HIFI_HAS_BACKLIGHT
#endif
#define HIFI_BOARD "core"
#define HIFI_FW_VERSION "0.1.0"
#define HIFI_UPSTREAM "squeezelite-esp32 master-v4.3 ee1720c"

#define I2C_PORT 1 /* squeezelite's system I2C (I2C_CONFIG): the DAC has no driver of its own */
#define I2C_SDA 13
#define I2C_SCL 14

/* I2S0 (squeezelite's DAC_CONFIG); I2S1 runs as a slave on the same clocks
 * and sends the sub DAC its data, so the PCM5102A costs one pin */
#define PIN_I2S_BCK 2
#define PIN_I2S_LRCK 4
#define PIN_I2S_DOUT_SUB 12 /* MTDI strap: the PCM5102A's DIN is high-Z at boot */
#define SUB_I2S_NUM 1

#define PIN_EXP_INT 39 /* the expander's INT, open drain, low = an input changed */
#define ADC_ISENSE ADC1_CHANNEL_6 /* GPIO34: INA186A1, 25 V/V over 10 mOhm */
#define ISENSE_V_PER_A 0.25f
#define ISENSE_RAW_FLOOR 8 /* ADC counts: under this the ADC is in its dead zone */

/* RMII and SMI: fixed by the ESP32's EMAC (and ETH_CONFIG in the patch);
 * here so the pin check reads them against the board too */
#define PIN_ETH_CLK 0    /* the 50 MHz oscillator in; it runs only while PHY_RST is high */
#define PIN_RMII_TXD0 19
#define PIN_RMII_TX_EN 21
#define PIN_RMII_TXD1 22
#define PIN_RMII_RXD0 25
#define PIN_RMII_RXD1 26
#define PIN_RMII_CRS_DV 27
#define PIN_MDC 23
#define PIN_MDIO 18

/* the I2C parts */
#define ES9018_ADDR 0x48 /* Sabre ES9018K2M, the mains DAC */
#define ES7243_ADDR 0x10 /* ES7243E, the line-in ADC: 0010 AD2 AD1 AD0, AD0/AD1 low; */
#define ES7243_ADDR_ALT 0x14 /* AD2 shares SDOUT, so the firmware tries both (known-unknowns parts:28) */
/* TCA9555 at 0x20 on the board as drawn; the first-spin review swaps in a
 * TCA9539 (same registers, a reset pin), whose address is 0x74-0x77.
 * The firmware takes the first that answers. */
#define EXP_ADDRS {0x20, 0x74, 0x75, 0x76, 0x77}
#define EXP_REG_IN0 0x00
#define EXP_REG_OUT0 0x02
#define EXP_REG_CFG0 0x06 /* 1 = input */

/* expander port 0: outputs, each with a 100k pull-down (off at reset) */
#define EXP_AMP_A_RST 0   /* high runs zone A's TPA3221 */
#define EXP_AMP_B_RST 1   /* zone B's (Ultra); release both in one write to sync them */
#define EXP_DJ_DIRECT 2   /* high: the line in goes straight to the amps */
#define EXP_PVDD_EN 3
#define EXP_DAC_EN 4      /* ES9018K2M RESETB and PCM5102A XSMT */
#define EXP_PHY_RST 5     /* the Ethernet clock's OE, and the LAN8720's nRST after it */
#define EXP_LCD_BL 6      /* Ultra's front board backlight */
#define EXP_LED 7         /* the red status LED */
/* port 1: inputs, pulled up (bit n is P1(n-8) in hifi_exp's 16 bits) */
#define EXP_AMP_FAULT 8   /* both amps' FAULT, wired-OR, low = fault */
#define EXP_AMP_OTW 9     /* OTW_CLIP, wired-OR, low = too hot or clipping */
#define EXP_ENC_A 10
#define EXP_ENC_B 11
#define EXP_ENC_SW 12     /* Plus: the knob's push */
#define EXP_BTN_1 13      /* Plus: source */
#define EXP_BTN_2 14      /* Plus: next */
#define EXP_TAP_SEL 15    /* P17 (TAP_SEL_IO), an output: low (the default, as Q7's base
                          * pull-down holds it) puts the ADC on the RCA line in, high on the
                          * speaker taps (C6; review-3 R3-DIGITAL-4) */
#define EXP_REG_OUT1 0x03
#define EXP_CFG0 0x00
#define EXP_CFG1 0x7F

/* Ultra's front board (boards/ultra-front): a TCA9535 at 0x27 on the same
 * I2C, its INT wired-OR onto EXP_INT, so every interrupt reads it too */
#define FRONT_ADDR 0x27
#define FRONT_ENC_SW 2    /* P02; P00/P01 are the knob, which core's own P12/P13 read */
#define FRONT_BTN_1 3     /* P03..P05, low = pressed (10k pull-ups) */
#define FRONT_LCD_RST 8   /* P10, high runs the panel (R8 pulls it up) */
#define FRONT_LED_R 9     /* P11..P13, the RGB LED's cathodes, low = lit; red off is an */
#define FRONT_LED_G 10    /* input, since 1.7 V could just light it (blocks.md B8) */
#define FRONT_LED_B 11
#define FRONT_DIM_MS 60000 /* the backlight goes off this long after a touch, when nothing plays */

#define TONE_RATE 48000

/* the line in: core's I2S0 runs 32-bit slots (DAC_CONFIG bits=32 in the
 * patch), so BCLK is 64 fs, the least the ES7243E takes as its clock */
#define LINE_SLOT_BITS 32
#define SUB_DMA_LEN 256   /* frames per buffer: matches I2S0's, so the subs line up with the mains */
#define SUB_DMA_COUNT 12
#define SUB_DIRECT_DMA_LEN 64 /* DJ direct: ~5 ms of buffer, so the subs follow the analog mains */
#define SUB_DIRECT_DMA_COUNT 4

/* what this board's firmware does besides the shared parts */
#define HIFI_HAS_CAPTURE 0 /* the API's capture is the ES8388's; core's ADC plays the line in instead */

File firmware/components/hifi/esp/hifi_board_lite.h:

/*
 * lite-main's pins and parts, from boards/lite/README.md (the board's own
 * pin map; agreed with its designer). Squeezelite-esp32 owns the codec's
 * I2S, the buttons, IR and the LED through the Kconfig defaults in
 * firmware/patches; this component owns the power path and the amp.
 */
#pragma once

#define HIFI_MODEL "hifi-lite"
#define HIFI_BOARD "lite-main"
#define HIFI_ZONES 1
#define HIFI_FW_VERSION "0.1.0"
#define HIFI_UPSTREAM "squeezelite-esp32 master-v4.3 ee1720c"

#define PIN_PD_PG 4      /* CH224A PG, open drain, low = contract good */
#define PIN_PVDD_EN 18   /* high closes the PVDD switch (ANDed with PG in hardware) */
#define PIN_AMP_SDZ 21   /* TPA3118 SDZ through R54 10k, high = run */
#define PIN_AMP_FAULTZ 23 /* TPA3118 FAULTZ, open drain, low = fault */
/* The ESP32's I2S outputs (squeezelite sets them up from DAC_CONFIG): only named
 * here to slow their edges, see hifi_bsp_init */
#define PIN_I2S_BCLK 27
#define PIN_I2S_LRCK 25
#define PIN_I2S_DOUT 26
#define ADC_VBUS ADC1_CHANNEL_6 /* GPIO34, VBUS / 11 (100k over 10k) */
#define VBUS_DIVIDER 11.0f
#define ADC_PVDD ADC1_CHANNEL_3 /* GPIO39 (SENSOR_VN), PVDD_SENSE: PVDD / 11 (R17 100k over R18 10k) */
#define PVDD_DIVIDER 11.0f

#define I2C_PORT 0       /* shared with squeezelite's codec driver */
#define I2C_SDA 33
#define I2C_SCL 32
#define ES8388_ADDR 0x10

/* ES8388 registers this component touches (datasheet rev 5.0) */
#define ES8388_ADCPOWER 0x03 /* bit7/6 power down the analog inputs */
#define ES8388_DACPOWER 0x04 /* bits 5..2: LOUT1 ROUT1 LOUT2 ROUT2 on */
#define ES8388_DACCONTROL17 0x27 /* left mixer: bit7 DAC, bit6 LIN, bits5:3 LIN gain */
#define ES8388_DACCONTROL20 0x2A /* right mixer, same layout */
#define ES8388_LOUT1VOL 0x2E /* speaker amp L: same scale as LOUT2 */
#define ES8388_ROUT1VOL 0x2F
/* the speaker outputs' highest code: 27 = -4.5 dB. The first-spin board review
 * (task 261029-020622, docs/review-2/firmware-requirements.md) caps LOUT1/ROUT1
 * at -4.5 dB and the line-in bypass at -3 dB: 0 dB overdrives the amp */
#define ES8388_OUT1_FULL 27
#define ES8388_MIX_LIN_M3DB 0x18 /* DACCONTROL17/20 bits 5:3 = 011: LIN at -3 dB */
#define ES8388_LOUT2VOL 0x30 /* sub out L: 0 = -45 dB, 30 = 0 dB, 33 = +4.5 dB */
#define ES8388_ROUT2VOL 0x31

#define TONE_RATE 48000

/* what this board's firmware does besides the shared parts */
#define HIFI_HAS_CAPTURE 1 /* the ES8388's ADC: line in and the loopback taps */

/* ES8388 ADC, for the captures (docs/remote.md). Values from the datasheet,
 * not yet checked on a board. */
#define ES8388_ADCCONTROL1 0x09  /* PGA gain, 0 = 0 dB */
#define ES8388_ADCCONTROL2 0x0A  /* bits 7:6 LINSEL, 5:4 RINSEL: 00 = input 1, 01 = input 2 */
#define ES8388_ADCCONTROL4 0x0C  /* I2S, 16 bit */
#define ES8388_ADCCONTROL5 0x0D  /* MCLK/LRCK 256 */
#define ES8388_ADCCONTROL8 0x10  /* left ADC digital volume, 0 = 0 dB */
#define ES8388_ADCCONTROL9 0x11
#define ES8388_ADCCONTROL10 0x12 /* bits 7:6 ALC: 00 = off */
#define ES8388_ADCPOWER_CAPTURE 0x08 /* inputs and ADCs on, mic bias off */

/* The loopback taps: each speaker's + leg through 100k over 10k into LIN2/RIN2.
 * The board the review-2 ECO built (and every one since) has them: R66-R69,
 * C81-C84. "hifi_taps"=0 in NVS turns them off for a board without. */
#ifndef HIFI_HAS_TAPS
#define HIFI_HAS_TAPS 1
#endif
/* 100k over 10k, loaded by the ES8388's LIN2/RIN2 input: 0.0625 of the
 * speaker leg (firmware requirement L6, review-2 AUDIO-13) */
#define TAP_DIVIDER 16.0f
#define ADC_FS_PEAK_V 1.27f    /* ES8388 ADC full scale at 0 dB PGA, about 0.9 Vrms: calibrate at bring-up */
#define LINE_DIVIDER 2.5f      /* the line in's 15k over 10k (R30/R31, review-2 AUDIO-7) */

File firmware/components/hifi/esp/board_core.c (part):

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		return false;
	}
	i2s_pin_config_t pins = {.mck_io_num = I2S_PIN_NO_CHANGE, .bck_io_num = I2S_PIN_NO_CHANGE,
				 .ws_io_num = I2S_PIN_NO_CHANGE, .data_out_num = PIN_I2S_DOUT_SUB,
				 .data_in_num = I2S_PIN_NO_CHANGE};
	i2s_set_pin(SUB_I2S_NUM, &pins);
	PIN_INPUT_ENABLE(GPIO_PIN_MUX_REG[PIN_I2S_BCK]);
	PIN_INPUT_ENABLE(GPIO_PIN_MUX_REG[PIN_I2S_LRCK]);
	/* a TX slave takes its clocks on the TX side's inputs (IDF's i2s_set_pin
	 * does the same: s_tx_bck_sig, s_tx_ws_sig) */
	esp_rom_gpio_connect_in_signal(PIN_I2S_BCK, I2S1O_BCK_IN_IDX, false);
	esp_rom_gpio_connect_in_signal(PIN_I2S_LRCK, I2S1O_WS_IN_IDX, false);
	/* fill the queue with silence, so it is as deep as I2S0's from the start */
	static const int32_t zero[2 * 64];
	size_t w = 0;
	for (int i = 0; i < c.dma_buf_count * c.dma_buf_len / 64; i++) i2s_write(SUB_I2S_NUM, zero, sizeof(zero), &w, 0);
	ESP_LOGI(TAG, "sub DAC on I2S%d, data on GPIO%d, %d frames queued%s", SUB_I2S_NUM, PIN_I2S_DOUT_SUB,
		 c.dma_buf_count * c.dma_buf_len, direct ? " (DJ direct: the ADC's samples)" : "");
	return true;
}
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/* Ultra's front board, left to right after the knob: knob push play/pause
 * (hold: standby), BTN1 input (hold: mute), BTN2 previous, BTN3 next. The
 * front's ENC_SW and BTN1-3 (its P02-P05) stand in for bits 12-15 of the
 * core's pins, where Plus has its own buttons and TAP_SEL */
#define FRONT_BITS 12
static const int PRESS[HIFI_EXP_BUTTONS] = {HIFI_IR_TOGGLE, HIFI_IR_INPUT, HIFI_IR_PREV, HIFI_IR_NEXT};
static const int HOLD[HIFI_EXP_BUTTONS] = {HIFI_IR_POWER, HIFI_IR_MUTE, -1, -1};
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static void controls(void *arg) {
	/* the decoder counts + when its enc_b changes first; Alps' EC11E turns clockwise
	 * with A leading (catalogue output waveform), so A goes in as enc_b (R5-UF-1) */
	hifi_exp_cfg_t cfg = {.enc_a = EXP_ENC_B, .enc_b = EXP_ENC_A, .edges_per_detent = 4,
#ifdef CONFIG_HIFI_ULTRA
			      .buttons = {FRONT_BITS, FRONT_BITS + 1, FRONT_BITS + 2, FRONT_BITS + 3},
#else
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
/* squeezelite has put I2S0's bit clock on its pin (the GPIO matrix says) */
static bool i2s0_on_pins(void) {
	uint32_t sel = REG_READ(GPIO_FUNC0_OUT_SEL_CFG_REG + 4 * PIN_I2S_BCK) & GPIO_FUNC0_OUT_SEL_M;
	return sel == I2S0O_BCK_OUT_IDX;
}

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void hifi_bsp_start(void) {
	if (exp_addr) {
		xTaskCreate(controls, "hifi_ctrl", 3072, NULL, ESP_TASK_PRIO_MIN + 3, &ctrl_task);
		gpio_config_t in = {.pin_bit_mask = BIT64(PIN_EXP_INT), .mode = GPIO_MODE_INPUT, .intr_type = GPIO_INTR_NEGEDGE};
		gpio_config(&in);
		gpio_isr_handler_add(PIN_EXP_INT, exp_isr, NULL); /* squeezelite installed the ISR service */
	}
	xTaskCreatePinnedToCore(sub_task, "hifi_sub", 3072, NULL, ESP_TASK_PRIO_MIN + 1, NULL, 1);
}
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void hifi_bsp_info(hifi_info_t *i) {
	i->psram_mb = heap_caps_get_total_size(MALLOC_CAP_SPIRAM) ? 8 : 0; /* WROVER-E N8R8 */
	i->caps = (hifi_caps_t) {
		.dj_direct = true, .line = true, .eq_min_db = -12, .eq_max_db = 12,
		.sub_count = 2, .sub_crossover = false, .sub_per_sub = false,
		.zones = HIFI_ZONES, .eth = true, .pdo_v_max = 28,
	};
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	hifi_selftest_add(t, "front_i2c", front, front ? "0x%02x acks" : "0x%02x doesn't answer (the FFC?)", FRONT_ADDR);
#endif
	bool otw = !(in_pins >> EXP_AMP_OTW & 1);
	hifi_selftest_add(t, "amp_otw", !otw, otw ? "OTW_CLIP low: too hot or clipping" : "OTW_CLIP high");
}

bool hifi_bsp_parts_ok(void) {
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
